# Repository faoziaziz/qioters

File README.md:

# qiot
 this is the kicad file to qriot

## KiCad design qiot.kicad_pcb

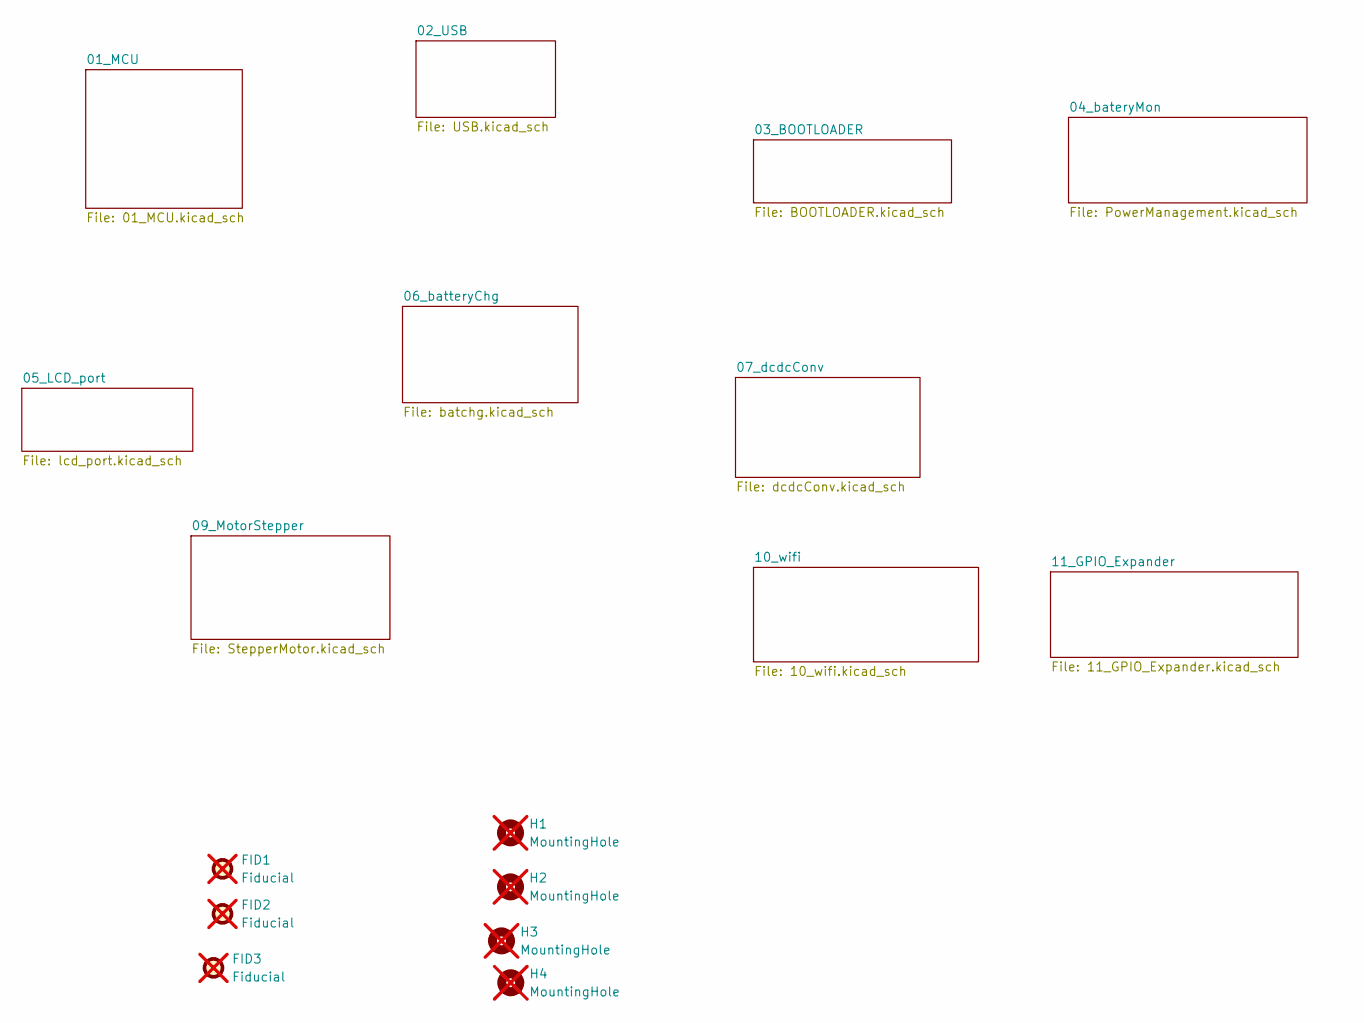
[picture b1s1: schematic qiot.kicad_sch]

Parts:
FID1, FID2, FID3: Fiducial; Fiducial_1.5mm_Mask3mm; not fitted
H1, H2, H3, H4: MountingHole; MountingHole_2.7mm_M2.5; not fitted

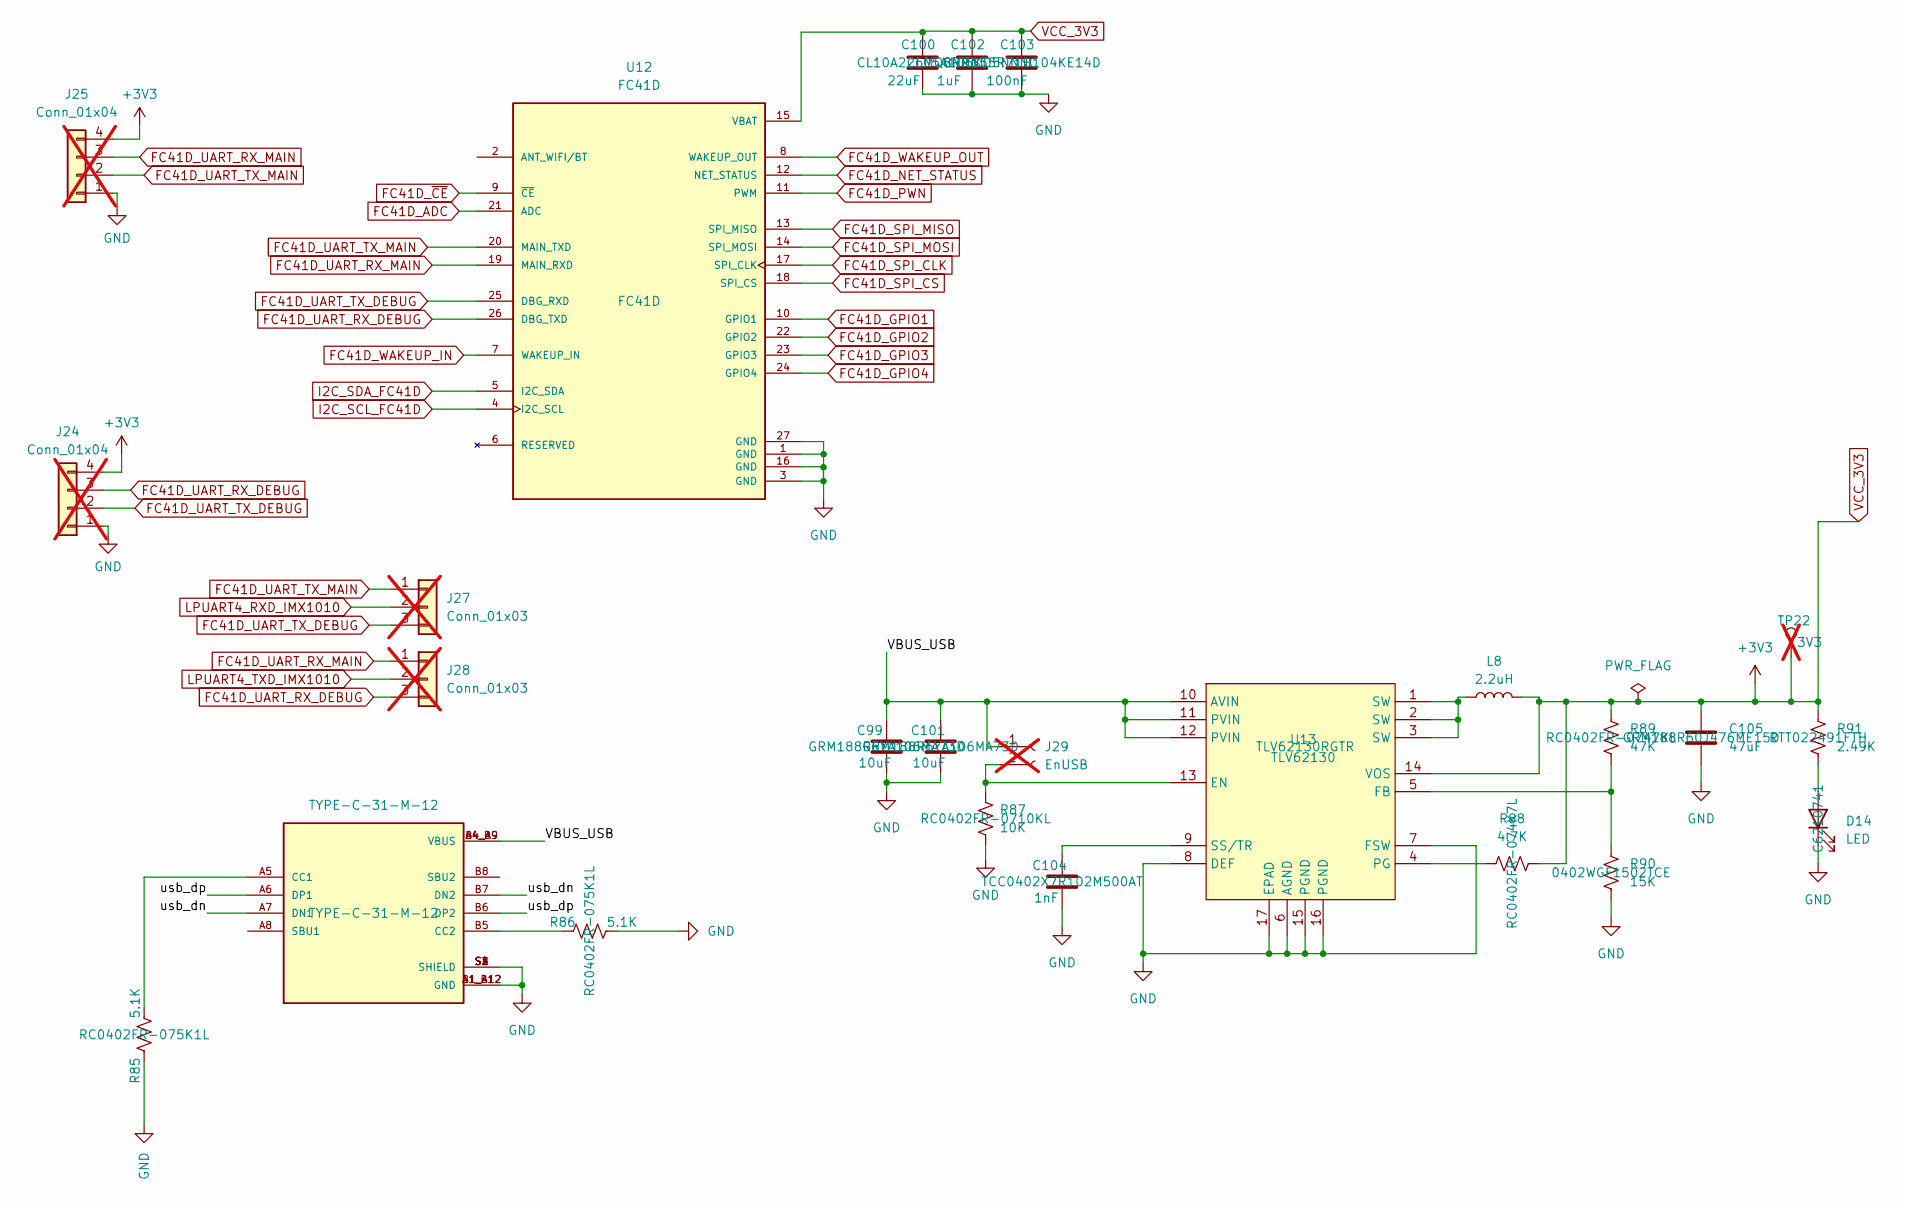
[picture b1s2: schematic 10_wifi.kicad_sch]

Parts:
C99, C101: 10uF; C_0603_1608Metric; Manufacturer_Part_Number GRM188R6YA106MA73D; LCSC Part # C194427
C100: 22uF; C_0603_1608Metric; Manufacturer_Part_Number CL10A226MQ8NRNC; LCSC Part # C59461
C102: 1uF; C_0402_1005Metric; Manufacturer_Part_Number CL05A105KO5NNNC; LCSC Part # C29266
C103: 100nF; C_0402_1005Metric; Manufacturer_Part_Number GRM155R71H104KE14D; LCSC Part # C77020
C104: 1nF; C_0402_1005Metric; Manufacturer_Part_Number TCC0402X7R102M500AT; LCSC Part # C696907
C105: 47uF; C_0603_1608Metric; Manufacturer_Part_Number GRM188R60J476ME15D; LCSC Part # C140782
D14: LED; LED_0402_1005Metric; Manufacturer_Part_Number C6210741; LCSC Part # C6210741
J24, J25: Conn_01x04; PinHeader_1x04_P2.54mm_Vertical; not fitted
J26: TYPE-C-31-M-12; HRO_TYPE-C-31-M-12; PARTREV 2020.12.08; LCSC Part # C165948
J27, J28: Conn_01x03; PinHeader_1x03_P2.54mm_Vertical; not fitted
J29: EnUSB; PinHeader_1x02_P2.54mm_Vertical; not fitted
L8: 2.2uH; LCSC part C108293
R85, R86: 5.1K; R_0402_1005Metric; Manufacturer_Part_Number RC0402FR-075K1L; LCSC Part # C105872
R87: 10K; R_0402_1005Metric; Manufacturer_Part_Number RC0402FR-0710KL; LCSC Part # C60490
R88: 4.7K; R_0402_1005Metric; Manufacturer_Part_Number RC0402FR-074K7L; LCSC Part # C105871
R89: 47K; R_0402_1005Metric; Manufacturer_Part_Number RC0402FR-0747KL; LCSC Part # C93943
R90: 15K; R_0402_1005Metric; Manufacturer_Part_Number 0402WGF1502TCE; LCSC Part # C25756
R91: 2.49K; R_0402_1005Metric; Manufacturer_Part_Number RTT022491FTH; LCSC Part # C102924
TP22: 3V3; TestPoint_Pad_D2.5mm; not fitted
U12: FC41D; XCVR_FC41D; PARTREV 1.0; LCSC Part # FC41D
U13: TLV62130; RGT0016C; Manufacturer_Part_Number TLV62130RGTR; LCSC Part # C122479

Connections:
/10_wifi/VBUS_USB: C99.1, C101.1, J26.A4_B9 (VBUS), J26.B4_A9 (VBUS), J29.1, U13.10 (AVIN), U13.11 (PVIN), U13.12 (PVIN)
/10_wifi/usb_dn: J26.A7 (DN1), J26.B7 (DN2)
/10_wifi/usb_dp: J26.A6 (DP1), J26.B6 (DP2)
FC41D_ADC: U12.21 (ADC)
FC41D_GPIO1: U12.10 (GPIO1)
FC41D_GPIO2: U12.22 (GPIO2)
FC41D_GPIO3: U12.23 (GPIO3)
FC41D_GPIO4: U12.24 (GPIO4)
FC41D_NET_STATUS: U12.12 (NET_STATUS)
FC41D_PWN: U12.11 (PWM)
FC41D_SPI_CLK: U12.17 (SPI_CLK)
FC41D_SPI_CS: U12.18 (SPI_CS)
FC41D_SPI_MISO: U12.13 (SPI_MISO)
FC41D_SPI_MOSI: U12.14 (SPI_MOSI)
FC41D_UART_RX_DEBUG: J24.3, J28.3, U12.26 (DBG_TXD)
FC41D_UART_RX_MAIN: J25.3, J28.1, U12.19 (MAIN_RXD)
FC41D_UART_TX_DEBUG: J24.2, J27.3, U12.25 (DBG_RXD)
FC41D_UART_TX_MAIN: J25.2, J27.1, U12.20 (MAIN_TXD)
FC41D_WAKEUP_IN: U12.7 (WAKEUP_IN)
FC41D_WAKEUP_OUT: U12.8 (WAKEUP_OUT)
FC41D_~CE: U12.9 (~CE)
I2C_SCL_FC41D: U12.4 (I2C_SCL)
I2C_SDA_FC41D: U12.5 (I2C_SDA)
LPUART4_RXD_IMX1010: J27.2; also elsewhere on the board
LPUART4_TXD_IMX1010: J28.2; also elsewhere on the board
unnamed: D14.2 (A), R91.1
unnamed: J26.A5 (CC1), R85.2
unnamed: J26.B5 (CC2), R86.2
unnamed: J29.2, R87.1, U13.13 (EN)
unnamed: R89.1, R90.2, U13.5 (FB)
unnamed: R88.1, U13.4 (PG)
unnamed: C104.1, U13.9 (SS/TR)
SYSN: C99.2, C100.2, C101.2, C102.2, C103.2, C104.2, C105.2, D14.1 (K), J24.1, J25.1, J26.A1_B12 (GND), J26.B1_A12 (GND), J26.S1 (SHIELD), J26.S2 (SHIELD), J26.S3 (SHIELD), J26.S4 (SHIELD), R85.1, R86.1, R87.2, R90.1, U12.1 (GND), U12.3 (GND), U12.16 (GND), U12.27 (GND), U13.6 (AGND), U13.7 (FSW), U13.8 (DEF), U13.15 (PGND), U13.16 (PGND), U13.17 (EPAD); also elsewhere on the board

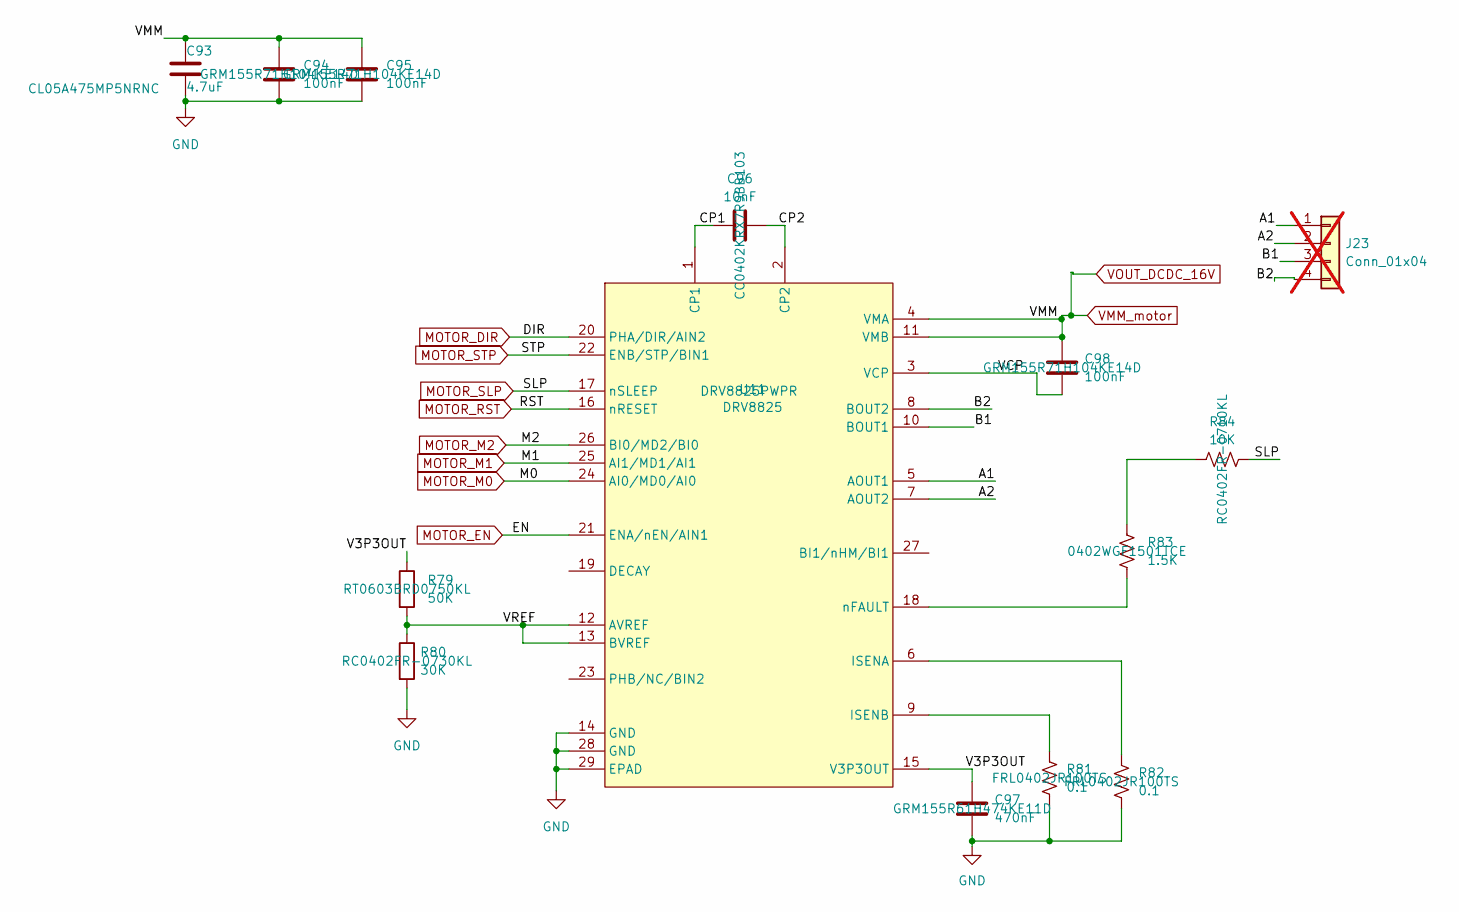
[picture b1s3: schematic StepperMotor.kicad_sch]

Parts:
C93: 4.7uF; C_0402_1005Metric; Manufacturer_Part_Number CL05A475MP5NRNC; LCSC Part # C23733
C94, C95, C98: 100nF; C_0402_1005Metric; Manufacturer_Part_Number GRM155R71H104KE14D; LCSC Part # C77020
C96: 10nF; C_0402_1005Metric; Manufacturer_Part_Number CC0402KRX7R9BB103; LCSC Part # C60133
C97: 470nF; C_0402_1005Metric; Manufacturer_Part_Number GRM155R61H474KE11D; LCSC Part # C437527
J23: Conn_01x04; PinSocket_1x04_P2.54mm_Vertical; not fitted
R79: 50K; R_0603_1608Metric; Manufacturer_Part_Number RT0603BRD0750KL; LCSC Part # C861451
R80: 30K; R_0402_1005Metric; Manufacturer_Part_Number RC0402FR-0730KL; LCSC Part # C138008
R81, R82: 0.1; R_0402_1005Metric; Manufacturer_Part_Number FRL0402JR100TS; LCSC Part # C3013344
R83: 1.5K; R_0402_1005Metric; Manufacturer_Part_Number 0402WGF1501TCE; LCSC Part # C25867
R84: 10K; R_0402_1005Metric; Manufacturer_Part_Number RC0402FR-0710KL; LCSC Part # C60490
U11: DRV8825; PWP28_5P18X3P1; Manufacturer_Part_Number DRV8825PWPR; LCSC Part # C81582

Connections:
/09_MotorStepper/A1: J23.1, U11.5 (AOUT1)
/09_MotorStepper/A2: J23.2, U11.7 (AOUT2)
/09_MotorStepper/B1: J23.3, U11.10 (BOUT1)
/09_MotorStepper/B2: J23.4, U11.8 (BOUT2)
/09_MotorStepper/CP1: C96.1, U11.1 (CP1)
/09_MotorStepper/CP2: C96.2, U11.2 (CP2)
/09_MotorStepper/V3P3OUT: C97.1, R79.1, U11.15 (V3P3OUT)
/09_MotorStepper/VCP: C98.2, U11.3 (VCP)
/09_MotorStepper/VREF: R79.2, R80.1, U11.12 (AVREF), U11.13 (BVREF)
MOTOR_DIR: U11.20 (PHA/DIR/AIN2); also elsewhere on the board
MOTOR_EN: U11.21 (ENA/nEN/AIN1); also elsewhere on the board
MOTOR_M0: U11.24 (AI0/MD0/AI0); also elsewhere on the board
MOTOR_M1: U11.25 (AI1/MD1/AI1); also elsewhere on the board
MOTOR_M2: U11.26 (BI0/MD2/BI0); also elsewhere on the board
MOTOR_RST: U11.16 (nRESET); also elsewhere on the board
MOTOR_SLP: R84.2, U11.17 (nSLEEP); also elsewhere on the board
MOTOR_STP: U11.22 (ENB/STP/BIN1); also elsewhere on the board
unnamed: R83.1, R84.1
unnamed: R82.1, U11.6 (ISENA)
unnamed: R81.1, U11.9 (ISENB)
unnamed: R83.2, U11.18 (nFAULT)
SYSN: C93.2, C94.2, C95.2, C97.2, R80.2, R81.2, R82.2, U11.14 (GND), U11.28 (GND), U11.29 (EPAD); also elsewhere on the board
VMM_motor: C93.1, C94.1, C95.1, C98.1, U11.4 (VMA), U11.11 (VMB); also elsewhere on the board

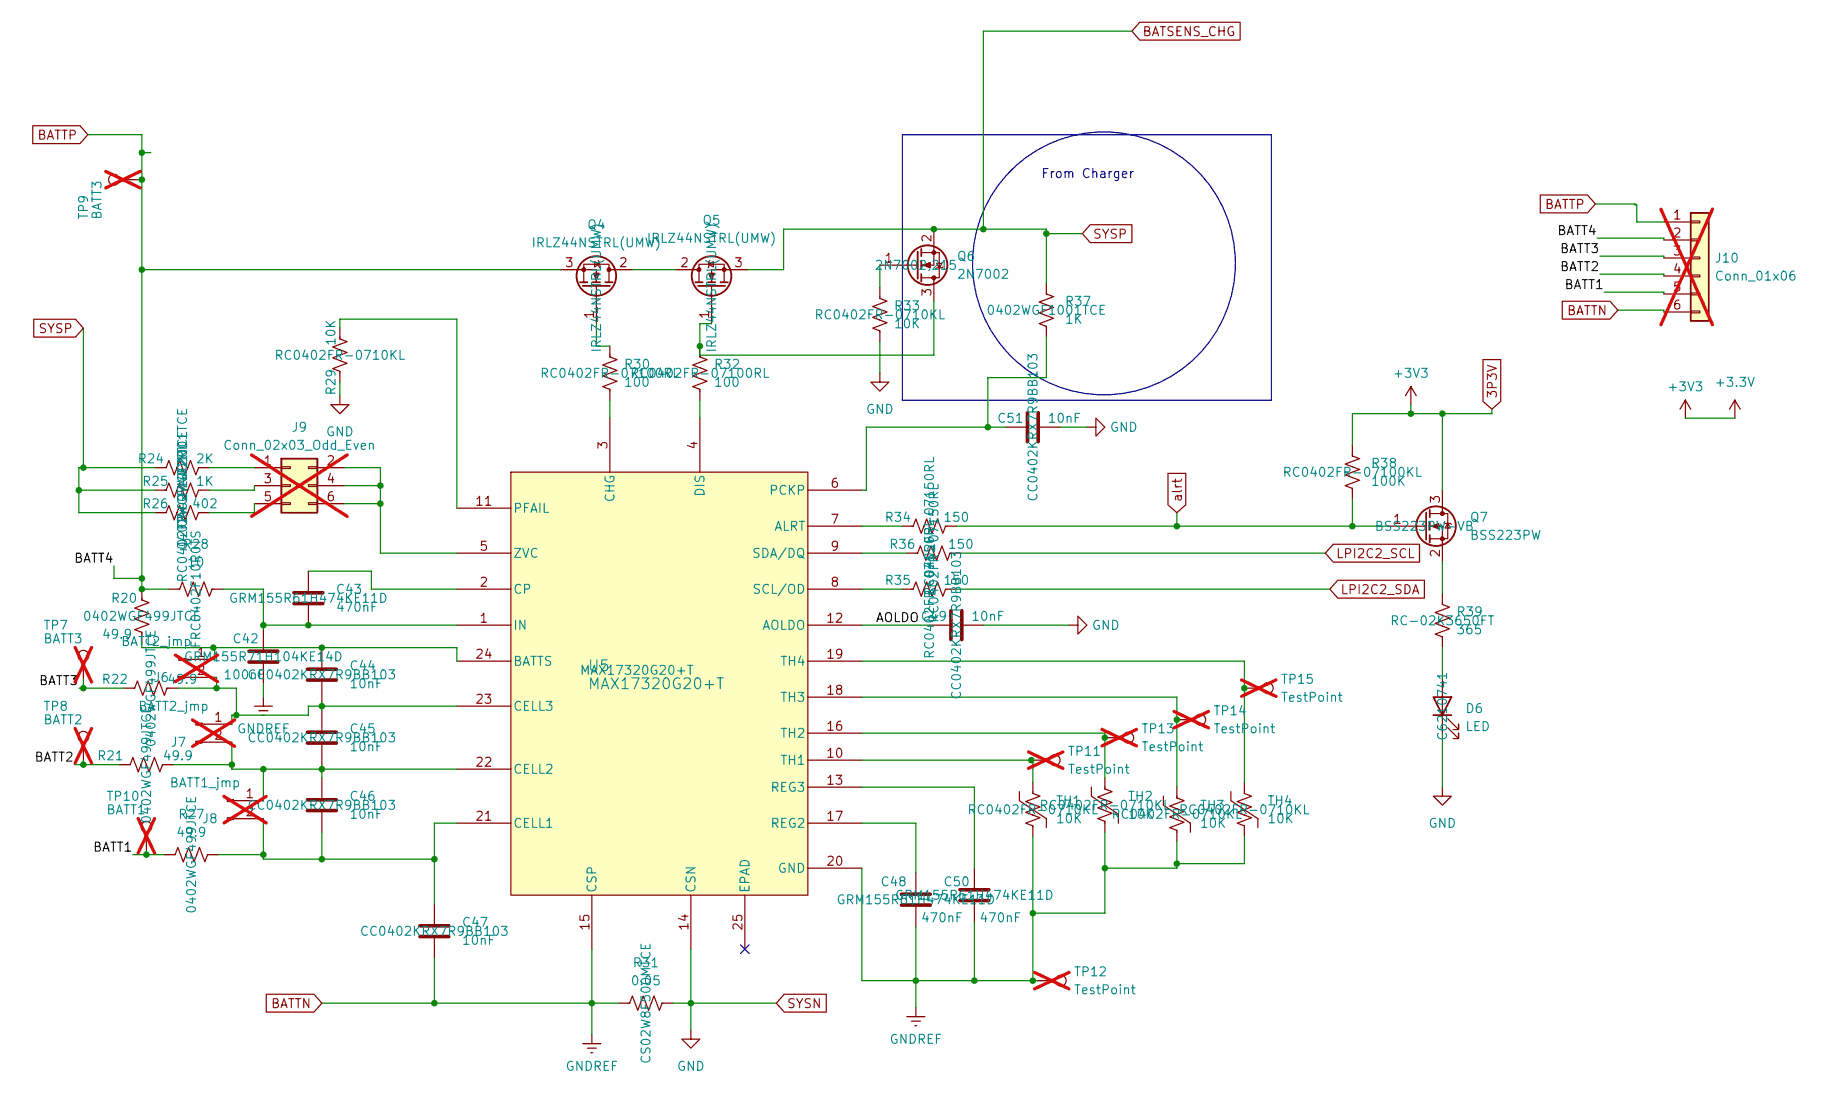
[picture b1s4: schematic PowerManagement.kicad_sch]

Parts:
C42: 100nF; C_0402_1005Metric; Manufacturer_Part_Number GRM155R71H104KE14D; LCSC Part # C77020
C43, C48, C50: 470nF; C_0402_1005Metric; Manufacturer_Part_Number GRM155R61H474KE11D; LCSC Part # C437527
C44, C45, C46, C47, C49, C51: 10nF; C_0402_1005Metric; Manufacturer_Part_Number CC0402KRX7R9BB103; LCSC Part # C60133
D6: LED; LED_0402_1005Metric; Manufacturer_Part_Number C6210741; LCSC Part # C6210741
J6, J7: BATT2_jmp; PinHeader_1x02_P2.54mm_Vertical; not fitted
J8: BATT1_jmp; PinHeader_1x02_P2.54mm_Vertical; not fitted
J9: Conn_02x03_Odd_Even; PinHeader_2x03_P2.54mm_Vertical; not fitted
J10: Conn_01x06; PinSocket_1x06_P2.54mm_Vertical; not fitted
Q4, Q5: IRLZ44NSTRL(UMW); TO-263-2; Manufacturer_Part_Number IRLZ44NSTRL(UMW); LCSC Part # C42370422
Q6: 2N7002; SOT-23; Manufacturer_Part_Number 2N7002,215; LCSC Part # C65189
Q7: BSS223PW; SOT-323_SC-70; Manufacturer_Part_Number BSS223PW-VB; LCSC Part # C5197341
R20, R21, R22, R27: 49.9; R_0402_1005Metric; Manufacturer_Part_Number 0402WGF499JTCE; LCSC Part # C25120
R24: 2K; R_0402_1005Metric; Manufacturer_Part_Number 0402WGF2001TCE; LCSC Part # C4109
R25, R37: 1K; R_0402_1005Metric; Manufacturer_Part_Number 0402WGF1001TCE; LCSC Part # C11702
R26: 402; R_0402_1005Metric; Manufacturer_Part_Number RC0402FR-07402RL; LCSC Part # C137984
R28: 10; R_0402_1005Metric; Manufacturer_Part_Number FRC0402F10R0TS; LCSC Part # C2906862
R29, R33: 10K; R_0402_1005Metric; Manufacturer_Part_Number RC0402FR-0710KL; LCSC Part # C60490
R30, R32: 100; R_0402_1005Metric; Manufacturer_Part_Number RC0402FR-07100RL; LCSC Part # C106232
R31: 0.05; R_0402_1005Metric; Manufacturer_Part_Number CS02W8F500MTCE; LCSC Part # C473658
R34, R35, R36: 150; R_0402_1005Metric; Manufacturer_Part_Number RC0402FR-07150RL; LCSC Part # C138054
R38: 100K; R_0402_1005Metric; Manufacturer_Part_Number RC0402FR-07100KL; LCSC Part # C60491
R39: 365; R_0402_1005Metric; Manufacturer_Part_Number RC-02K3650FT; LCSC Part # C453662
TH1: 10K; R_0402_1005Metric; Manu Part NCP15XH103F03RC; LCSC Part # C60490
TH2, TH3, TH4: 10K; R_0402_1005Metric; Manufacturer_Part_Number RC0402FR-0710KL; LCSC Part # C60490
TP7, TP9: BATT3; TestPoint_Pad_D2.5mm; not fitted
TP8: BATT2; TestPoint_Pad_D2.5mm; not fitted
TP10: BATT1; TestPoint_Pad_D2.5mm; not fitted
TP11, TP12, TP13, TP14, TP15: TestPoint; TestPoint_Pad_D2.5mm; not fitted
U5: MAX17320G20+T; 21-0139I_T2444-4_MXM; Manufacturer_Part_Number MAX17320G20+T; LCSC Part # C7457895

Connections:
/04_bateryMon/AOLDO: C49.1, U5.12 (AOLDO)
/04_bateryMon/BATT1: J10.5, R27.1, TP10.1
/04_bateryMon/BATT2: J10.4, R21.1, TP8.1
/04_bateryMon/BATT3: J10.3, R22.1, TP7.1
BATSENS_CHG: Q5.3 (S), Q6.2 (S), R24.1, R25.1, R26.1, R37.1; also elsewhere on the board
BATTN: C42.2, C47.2, C48.2, C50.2, J10.6, R31.1, TH1.2, TH2.2, TH3.2, TH4.2, TP12.1, U5.15 (CSP), U5.20 (GND)
BATTP: J10.1, J10.2, Q4.3 (S), R20.1, R28.1, TP9.1
LPI2C2_SCL: R36.2; also elsewhere on the board
LPI2C2_SDA: R35.2; also elsewhere on the board
unnamed: D6.2 (A), R39.2
unnamed: C44.1, J6.1, R20.2, U5.24 (BATTS)
unnamed: C44.2, C45.1, J6.2, J7.1, R22.2, U5.23 (CELL3)
unnamed: C45.2, C46.1, J7.2, J8.1, R21.2, U5.22 (CELL2)
unnamed: C46.2, C47.1, J8.2, R27.2, U5.21 (CELL1)
unnamed: J9.1, R24.2
unnamed: J9.2, J9.4, J9.6, U5.5 (ZVC)
unnamed: J9.3, R25.2
unnamed: J9.5, R26.2
unnamed: Q4.2 (D), Q5.2 (D)
unnamed: Q4.1 (G), R30.1
unnamed: Q5.1 (G), Q6.3 (D), R32.1
unnamed: Q6.1 (G), R33.1
unnamed: Q7.2 (S), R39.1
unnamed: R34.1, U5.7 (ALRT)
unnamed: R30.2, U5.3 (CHG)
unnamed: C43.1, U5.2 (CP)
unnamed: R32.2, U5.4 (DIS)
unnamed: C42.1, C43.2, R28.2, U5.1 (IN)
unnamed: C51.1, R37.2, U5.6 (PCKP)
unnamed: R29.2, U5.11 (PFAIL)
unnamed: C48.1, U5.17 (REG2)
unnamed: C50.1, U5.13 (REG3)
unnamed: R35.1, U5.8 (SCL/OD)
unnamed: R36.1, U5.9 (SDA/DQ)
unnamed: TH1.1, TP11.1, U5.10 (TH1)
unnamed: TH2.1, TP13.1, U5.16 (TH2)
unnamed: TH3.1, TP14.1, U5.18 (TH3)
unnamed: TH4.1, TP15.1, U5.19 (TH4)
SYSN: C49.2, C51.2, D6.1 (K), R29.1, R31.2, R33.2, U5.14 (CSN); also elsewhere on the board
alrt: Q7.1 (G), R34.2, R38.2

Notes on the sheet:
From Charger

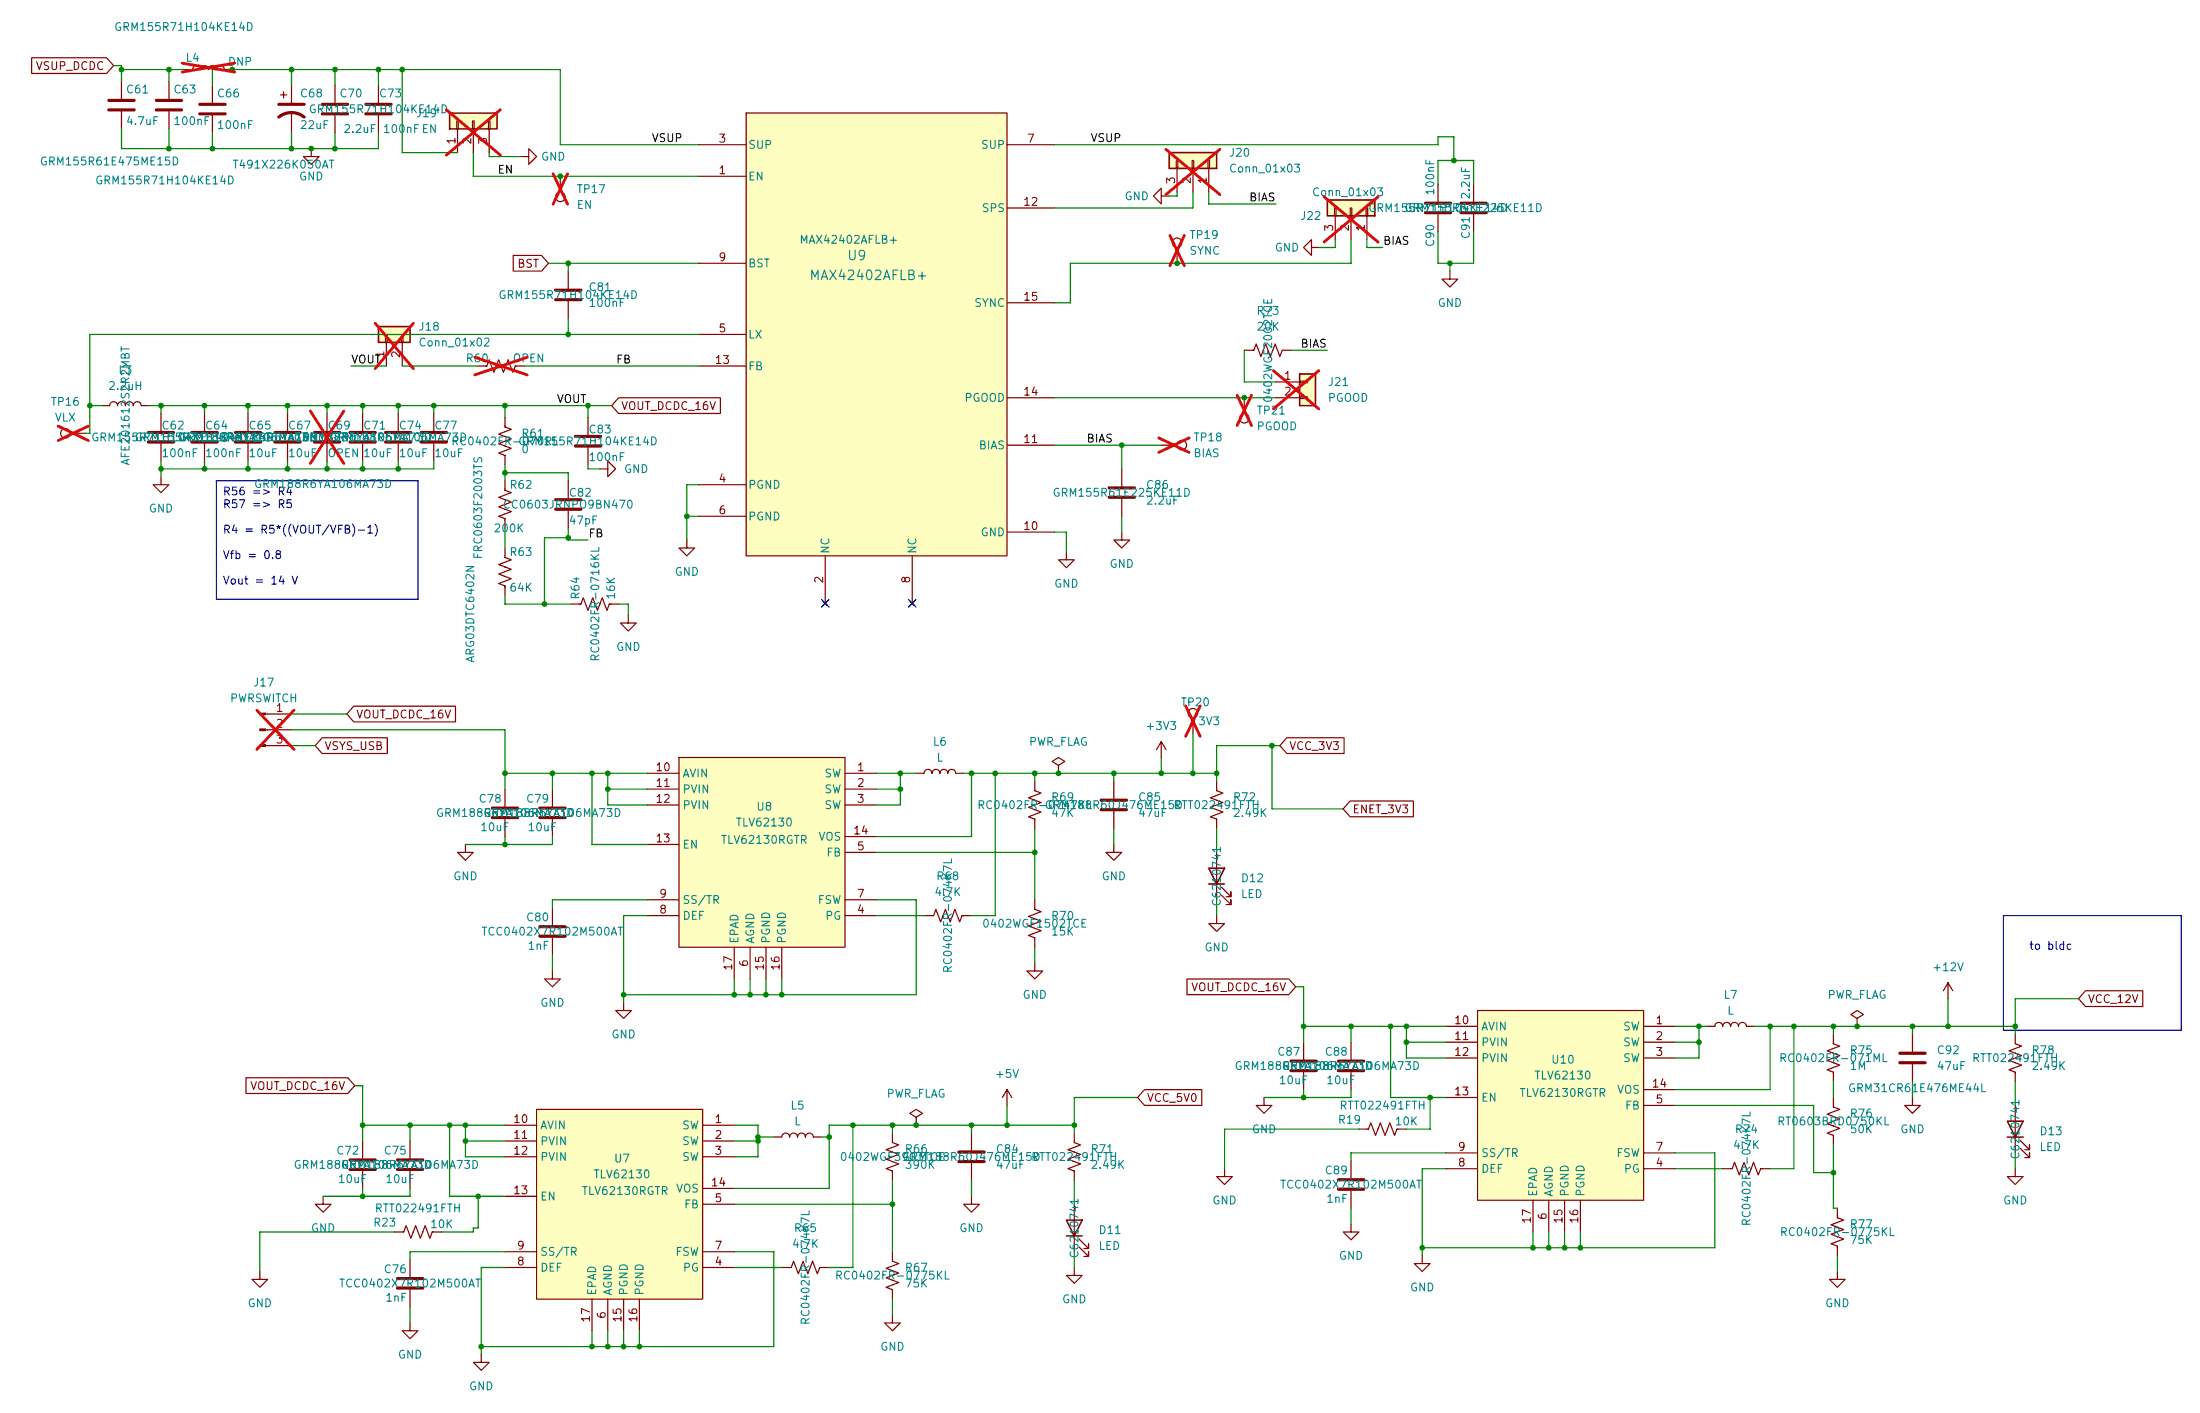
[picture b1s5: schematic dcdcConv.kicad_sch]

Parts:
C61: 4.7uF; C_0402_1005Metric; Manufacturer_Part_Number GRM155R61E475ME15D; LCSC Part # C2858031
C62, C63, C64, C66, C73, C81, C83, C90: 100nF; C_0402_1005Metric; Manufacturer_Part_Number GRM155R71H104KE14D; LCSC Part # C77020
C65, C67, C71, C72, C74, C75, C77, C78, C79, C87, C88: 10uF; C_0603_1608Metric; Manufacturer_Part_Number GRM188R6YA106MA73D; LCSC Part # C194427
C68: 22uF; CAP-SMD_L7.3-W4.3-R-RD; Manufacturer_Part_Number T491X226K050AT; LCSC Part # C696800
C69: OPEN; C_0603_1608Metric; not fitted
C70, C86, C91: 2.2uF; C_0402_1005Metric; Manufacturer_Part_Number GRM155R61E225KE11D; LCSC Part # C385032
C76, C80, C89: 1nF; C_0402_1005Metric; Manufacturer_Part_Number TCC0402X7R102M500AT; LCSC Part # C696907
C82: 47pF; C_0603_1608Metric; Manufacturer_Part_Number CC0603JRNPO9BN470; LCSC Part # C105622
C84, C85: 47uF; C_0603_1608Metric; Manufacturer_Part_Number GRM188R60J476ME15D; LCSC Part # C140782
C92: 47uF; C_1206_3216Metric; Manufacturer_Part_Number GRM31CR61E476ME44L; LCSC Part # C403725
D11, D12, D13: LED; LED_0402_1005Metric; Manufacturer_Part_Number C6210741; LCSC Part # C6210741
J17: PWRSWITCH; PinHeader_1x03_P2.54mm_Vertical; not fitted
J18: Conn_01x02; PinHeader_1x02_P2.54mm_Vertical; not fitted
J19: EN; PinHeader_1x03_P2.54mm_Vertical; not fitted
J20, J22: Conn_01x03; PinHeader_1x03_P2.54mm_Vertical; not fitted
J21: PGOOD; PinSocket_1x02_P2.54mm_Vertical; not fitted
L3: 2.2uH; L_APV_APH0620; Manufacturer_Part_Number AFE201612S2R2MBT; LCSC Part # C41347750
L4: DNP; L_APV_APH0620; not fitted
L5, L6, L7: L
R19, R23: 10K; R_0402_1005Metric; Manufacturer_Part_Number RTT022491FTH; LCSC Part # C102924
R60: OPEN; R_0402_1005Metric; not fitted
R61: 0; R_0402_1005Metric; Manufacturer_Part_Number RC0402FR-070RL; LCSC Part # C106231
R62: 200K; R_0603_1608Metric; Manufacturer_Part_Number FRC0603F2003TS; LCSC Part # C2907009
R63: 64K; R_0603_1608Metric; Manufacturer_Part_Number ARG03DTC6402N; LCSC Part # C2902643
R64: 16K; R_0402_1005Metric; Manufacturer_Part_Number RC0402FR-0716KL; LCSC Part # C163487
R65, R68, R74: 4.7K; R_0402_1005Metric; Manufacturer_Part_Number RC0402FR-074K7L; LCSC Part # C105871
R66: 390K; R_0402_1005Metric; Manufacturer_Part_Number 0402WGF3903TCE; LCSC Part # C25782
R67, R77: 75K; R_0402_1005Metric; Manufacturer_Part_Number RC0402FR-0775KL; LCSC Part # C137935
R69: 47K; R_0402_1005Metric; Manufacturer_Part_Number RC0402FR-0747KL; LCSC Part # C93943
R70: 15K; R_0402_1005Metric; Manufacturer_Part_Number 0402WGF1502TCE; LCSC Part # C25756
R71, R72, R78: 2.49K; R_0402_1005Metric; Manufacturer_Part_Number RTT022491FTH; LCSC Part # C102924
R73: 20K; R_0402_1005Metric; Manufacturer_Part_Number 0402WGF2002TCE; LCSC Part # C25765
R75: 1M; R_0402_1005Metric; Manufacturer_Part_Number RC0402FR-071ML; LCSC Part # C138033
R76: 50K; R_0603_1608Metric; Manufacturer_Part_Number RT0603BRD0750KL; LCSC Part # C861451
TP16: VLX; TestPoint_Pad_D2.5mm; not fitted
TP17: EN; TestPoint_Pad_D2.5mm; not fitted
TP18: BIAS; TestPoint_Pad_D2.5mm; not fitted
TP19: SYNC; TestPoint_Pad_D2.5mm; not fitted
TP20: 3V3; TestPoint_Pad_D2.5mm; not fitted
TP21: PGOOD; TestPoint_Pad_D2.5mm; not fitted
U7, U8, U10: TLV62130; RGT0016C; Manufacturer_Part_Number TLV62130RGTR; LCSC Part # C122479
U9: MAX42402AFLB+; MAX42402AFLB; Manufacturer_Part_Number MAX42402AFLB+; LCSC Part # C22392296

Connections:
/07_dcdcConv/BIAS: C86.1, J20.1, J22.1, R73.2, TP18.1, U9.11 (BIAS)
/07_dcdcConv/EN: J19.2, TP17.1, U9.1 (EN)
/07_dcdcConv/FB: C82.2, R60.2, R63.2, R64.1, U9.13 (FB)
/07_dcdcConv/VSUP: C66.1, C68.1, C70.1, C73.1, C90.1, C91.1, J19.1, L4.2, U9.3 (SUP), U9.7 (SUP)
BST: C81.1, U9.9 (BST)
unnamed: C82.1, R61.2, R62.1
unnamed: D11.2 (A), R71.1
unnamed: D12.2 (A), R72.1
unnamed: D13.2 (A), R78.1
unnamed: C78.1, C79.1, J17.2, U8.10 (AVIN), U8.11 (PVIN), U8.12 (PVIN), U8.13 (EN)
unnamed: J18.2, R60.1
unnamed: J20.2, U9.12 (SPS)
unnamed: J21.1, R73.1
unnamed: J21.2, TP21.1, U9.14 (PGOOD)
unnamed: J22.2, TP19.1, U9.15 (SYNC)
unnamed: R62.2, R63.1
unnamed: R75.1, R76.1
unnamed: R66.1, R67.2, U7.5 (FB)
unnamed: R65.1, U7.4 (PG)
unnamed: C76.1, U7.9 (SS/TR)
unnamed: R69.1, R70.2, U8.5 (FB)
unnamed: R68.1, U8.4 (PG)
unnamed: C80.1, U8.9 (SS/TR)
unnamed: C81.2, L3.1, TP16.1, U9.5 (LX)
unnamed: R76.2, R77.2, U10.5 (FB)
unnamed: R74.1, U10.4 (PG)
unnamed: C89.1, U10.9 (SS/TR)
SYSN: C61.2, C62.2, C63.2, C64.2, C65.2, C66.2, C67.2, C68.2, C69.2, C70.2, C71.2, C72.2, C73.2, C74.2, C75.2, C76.2, C77.2, C78.2, C79.2, C80.2, C83.2, C84.2, C85.2, C86.2, C87.2, C88.2, C89.2, C90.2, C91.2, C92.2, D11.1 (K), D12.1 (K), D13.1 (K), J19.3, J20.3, J22.3, R19.2, R23.2, R64.2, R67.1, R70.1, R77.1, U7.6 (AGND), U7.7 (FSW), U7.8 (DEF), U7.15 (PGND), U7.16 (PGND), U7.17 (EPAD), U8.6 (AGND), U8.7 (FSW), U8.8 (DEF), U8.15 (PGND), U8.16 (PGND), U8.17 (EPAD), U9.4 (PGND), U9.6 (PGND), U9.10 (GND), U10.6 (AGND), U10.7 (FSW), U10.8 (DEF), U10.15 (PGND), U10.16 (PGND), U10.17 (EPAD); also elsewhere on the board
VMM_motor: C62.1, C64.1, C65.1, C67.1, C69.1, C71.1, C72.1, C74.1, C75.1, C77.1, C83.1, C87.1, C88.1, J17.1, J18.1, L3.2, R19.1, R23.1, R61.1, U7.10 (AVIN), U7.11 (PVIN), U7.12 (PVIN), U7.13 (EN), U10.10 (AVIN), U10.11 (PVIN), U10.12 (PVIN), U10.13 (EN); also elsewhere on the board
VOUT_BATCHG: C61.1, C63.1, L4.1; also elsewhere on the board
VSYS_USB: J17.3; also elsewhere on the board

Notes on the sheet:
to bldc
R56 => R4 R57 => R5 R4 = R5*((VOUT/VFB)-1) Vfb = 0.8 Vout = 14 V

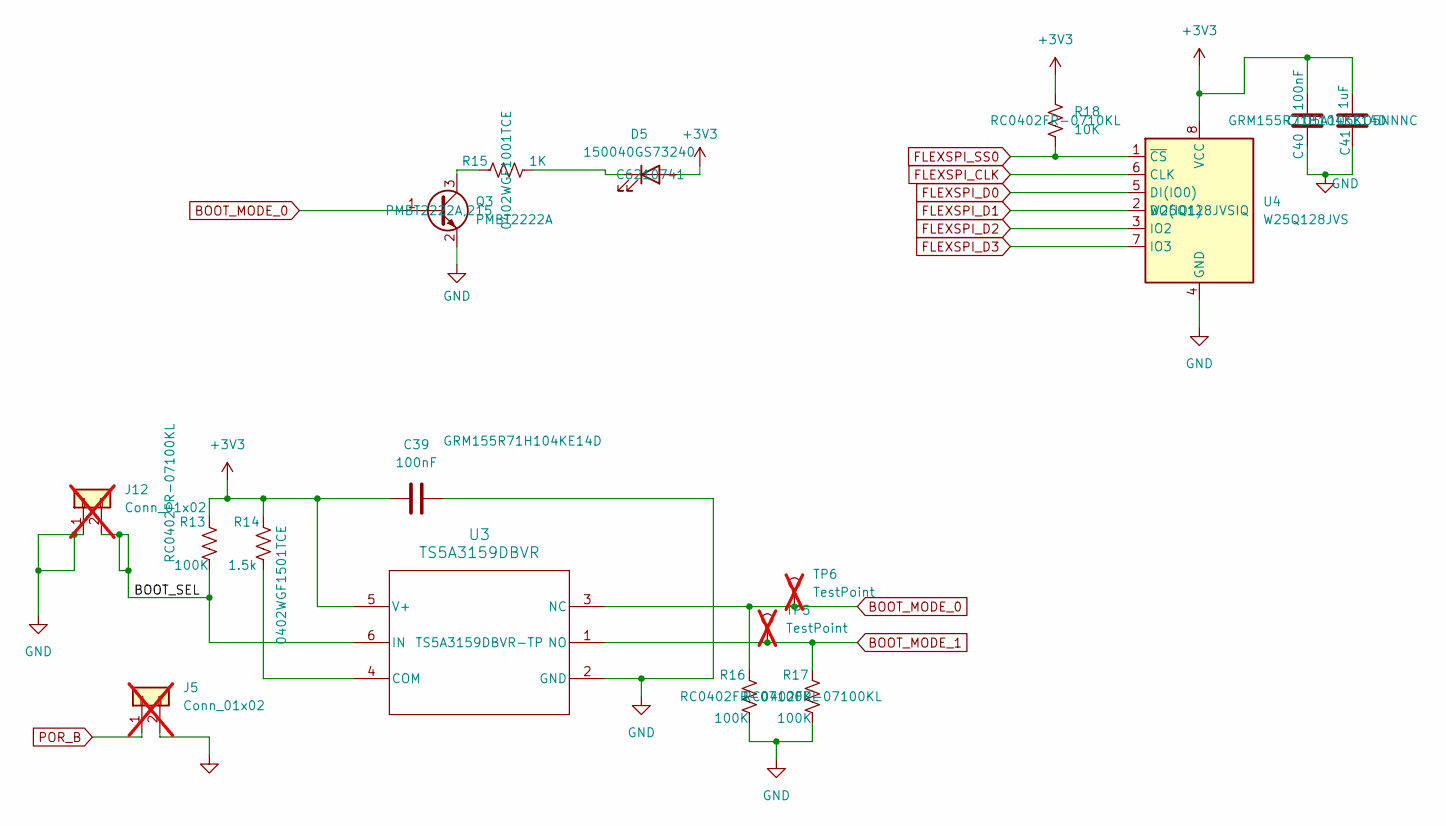
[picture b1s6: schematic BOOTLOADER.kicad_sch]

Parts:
C39, C40: 100nF; C_0402_1005Metric; Manufacturer_Part_Number GRM155R71H104KE14D; LCSC Part # C77020
C41: 1uF; C_0402_1005Metric; Manufacturer_Part_Number CL05A105KO5NNNC; LCSC Part # C29266
D5: 150040GS73240; LED_0402_1005Metric; Manufacturer_Part_Number C6210741; LCSC Part # C6210741
J5, J12: Conn_01x02; PinHeader_1x02_P2.54mm_Vertical; not fitted
Q3: PMBT2222A; SOT-23; Manufacturer_Part_Number PMBT2222A,215; LCSC Part # C23869
R13, R16, R17: 100K; R_0402_1005Metric; Manufacturer_Part_Number RC0402FR-07100KL; LCSC Part # C60491
R14: 1.5k; R_0402_1005Metric; Manufacturer_Part_Number 0402WGF1501TCE; LCSC Part # C25867
R15: 1K; R_0402_1005Metric; Manufacturer_Part_Number 0402WGF1001TCE; LCSC Part # C11702
R18: 10K; R_0402_1005Metric; Manufacturer_Part_Number RC0402FR-0710KL; LCSC Part # C60490
TP5, TP6: TestPoint; TestPoint_Pad_D2.5mm; not fitted
U3: TS5A3159DBVR; SOT-23-6; Manufacturer_Part_Number TS5A3159DBVR-TP; LCSC Part # C42411032
U4: W25Q128JVS; SOIC127P790X216-8N; Manufacturer_Part_Number W25Q128JVSIQ; LCSC Part # C97521

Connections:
/03_BOOTLOADER/BOOT_SEL: J12.2, R13.2, U3.6 (IN)
BOOT_MODE_0: Q3.1 (B), R16.1, TP6.1, U3.3 (NC); also elsewhere on the board
BOOT_MODE_1: R17.1, TP5.1, U3.1 (NO); also elsewhere on the board
FLEXSPI_CLK: U4.6 (CLK); also elsewhere on the board
FLEXSPI_D0: U4.5 (DI(IO0)); also elsewhere on the board
FLEXSPI_D1: U4.2 (DO(IO1)); also elsewhere on the board
FLEXSPI_D2: U4.3 (IO2); also elsewhere on the board
FLEXSPI_D3: U4.7 (IO3); also elsewhere on the board
FLEXSPI_SS0: R18.2, U4.1 (~CS); also elsewhere on the board
JTAG_RESET: J5.1; also elsewhere on the board
unnamed: D5.1 (K), R15.2
unnamed: Q3.3 (C), R15.1
unnamed: R14.2, U3.4 (COM)
SYSN: C39.2, C40.2, C41.2, J5.2, J12.1, Q3.2 (E), R16.2, R17.2, U3.2 (GND), U4.4 (GND); also elsewhere on the board

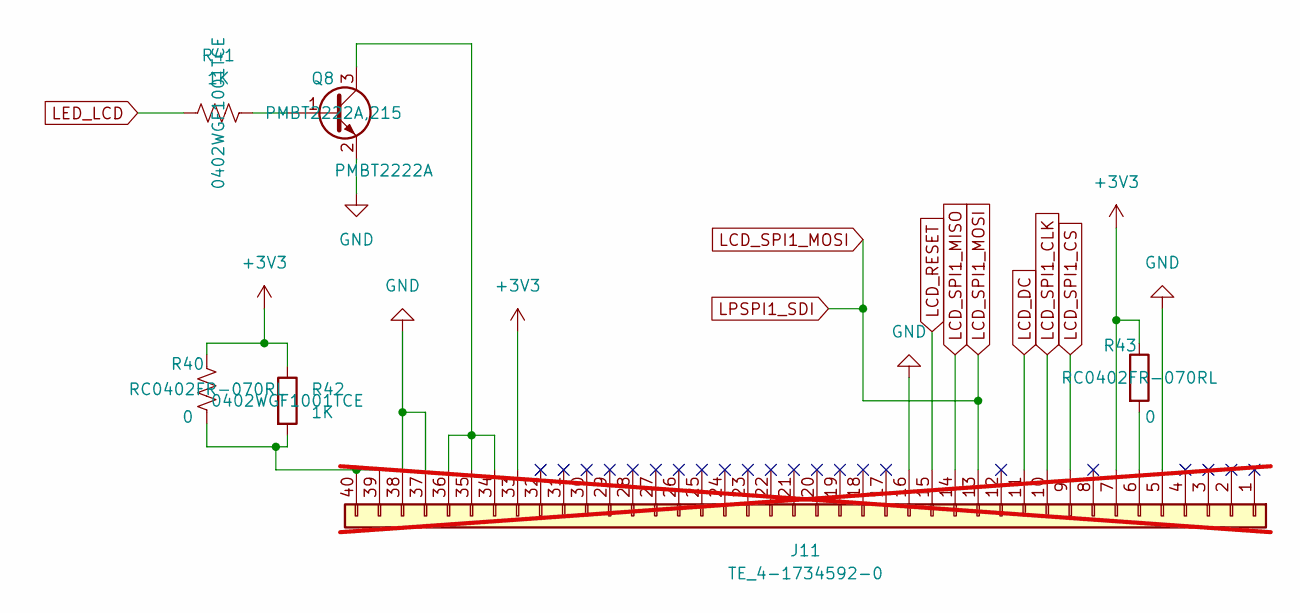
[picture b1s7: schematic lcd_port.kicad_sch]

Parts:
J11: TE_4-1734592-0; not fitted
Q8: PMBT2222A; SOT-23; Manufacturer_Part_Number PMBT2222A,215; LCSC Part # C23869
R40, R43: 0; R_0402_1005Metric; Manufacturer_Part_Number RC0402FR-070RL; LCSC Part # C106231
R41, R42: 1K; R_0402_1005Metric; Manufacturer_Part_Number 0402WGF1001TCE; LCSC Part # C11702

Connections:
JTAG_RESET: J11.15; also elsewhere on the board
LCD_DC: J11.11; also elsewhere on the board
LCD_SPI1_CLK: J11.10; also elsewhere on the board
LCD_SPI1_CS: J11.9; also elsewhere on the board
LCD_SPI1_MISO: J11.14; also elsewhere on the board
LCD_SPI1_MOSI: J11.13; also elsewhere on the board
LED_LCD: R41.1; also elsewhere on the board
unnamed: J11.6, R43.2
unnamed: J11.34, J11.35, J11.36, Q8.3 (C)
unnamed: J11.39, J11.40, R40.2, R42.2
unnamed: Q8.1 (B), R41.2
SYSN: J11.5, J11.16, J11.37, J11.38, Q8.2 (E); also elsewhere on the board
